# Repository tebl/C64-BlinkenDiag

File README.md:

# C64 BlinkenDiag
I was halfway through sketching out a new PCB based on the details found in an article on [tech.guitarsite.de](http://tech.guitarsite.de/c64_diag_dt_cart.html) before realizing it was already a PCB mentioned at the bottom, more specifically the one by [Diag64cart](https://github.com/svenpetersen1965/Diag64cart) by Sven Petersen (in turn based on [VersaCart64](https://github.com/bwack/Versa64Cart). I did however choose to introduce a few simple features of my own, mainly adding the option of disabling ROM boot - the method used was based on details found on [markus.brenner.de/cartridge](http://markus.brenner.de/cartridge). Secondly, I added a lot of LEDs in the hope that it might in some way be used to detect bus errors.

- [1> Building the unit](#1-building-the-unit)
  - [1.1> Soldering it together](#11-soldering-it-together)
  - [1.2> Assembling the unit](#12-assembling-the-unit)
  - [1.3> Testing it out](#13-testing-it-out)
- [2> Schematic](#2-schematic)
- [3> BOM](#3-bom)

# 1> Building the unit
Building the unit assumes you have at least minor experience soldering things together, recommended is at least a soldering station with adjustable temperature to get started - usually you'll want some 60/40 solder tin (if you can get that where you live). With the equipment sorted, now comes the shopping. So head on over to the [BOM](#3-bom)-section for some information on what you need, with ebay, AliExpress and similar sites you'll need to treat these as a starting search term and get what seems to match the gallery pictures.

## 1.1> Soldering it together
Every part already accounted for? Good, then let's start by not burning the house down (unless it obviously has more than one snake in it). Start by soldering in the resistors, there should only be a few of these on the board - follow it all up by tackling the resistor networks onto the boards, these are all the same type and you should match up the dot on them with the square hole. If you want to install sockets for all of the ICs, then that is good - if not, then please reconsider your life choices about now. Sockets need to match up with the markings on the PCB, indent on the socket should match the half-moon indent on the PCB (use machined sockets if you like that sort of thing).

Add the capacitors that are next to the sockets, these are only for decoupling and are not of the kind that is polarized - personally I tend to solder them in so that, if possible, you can see the printing on the side. The electrolytic capacitor on the bottom left corner, but we need to check that we have a component that will fit first - the faceplate will sit 8mm above the main PCB. If you have one that won't fit, you can lay it on its side instead of waiting for the slow boat from China. Note that this component is polarized, what this means is that you need to match the stripe with the filled in white space on the silkscreen.

Now we need to start the long and arduous task of soldering in all of those LEDs, but before we can do so - you  should probably check that they all work, the easiest way is to just use a CR2032 battery and putting it between the legs of the LED. Testing them will avoid soldering in one that is significantly more dim than the rest, especially if you originally got a whole shopping bag full of them for a single Dollar, Euro, Pound or whatever it is you usually fling at shopping attendants (please don't actually do this). One of the legs is called an anode and the other a cathode, but I can never remember which is which - so I'll just say that the short pin goes into the square hole. Only solder on one of the pins, then flip the board over again and heat up the pin by using your finger to push it flush against the board - this ensures that the faceplate will fit properly and you won't have a board where everything looks crooked.

SW1, 2 and 3 are a common AliExpress variety of DPDT 6-pin switches that needs some further explenation. The ones I've used here have a black base, the ones with a different colour will unfortunately not work as the pinouts have been shuffled around so ensure that you have the correct one ready to go. There is a square hole on the bottom that can be matched to the PCB illustration, just make sure that it goes into place with the hole at the top. There are also some keycaps floating around, but these fit rather loosely and I've taken to adding a drop of glue on the top of the switch to ensure that it doesn't go flying off. The reset switch is a more common momentary switch, the only requirement is that it is long enough to poke through the faceplate (6x6x9mm should fit, get a larger one if you require a bit than just barely).

## 1.2> Assembling the unit
Insert ICs into the sockets as indicated, ensuring that the indent matches the orientation on the board - plugging them in the wrong way ensures that you'll have to order some more. Double-check before even considering plugging it into something, use the picture below as reference. Even more important, study the board under good lighting condition in order to determine whether any stray blobs of solder has ended up in the wrong place - you're supposed to fix your C64, not add to its growing list of problems!

At this point I've not mentioned the EEPROM socket - it is designed for a 28C256, not 27C256 as used in many similar designs (mainly because I hate using UV to erase things and I have enough of them). You'll need an EPROM Programmer to put the machine code onto the chip, the one I use is one of the cheaper options - the MiniPro TL866. Using the *MiniPro Programmer* software (or similar), click the button below *Select IC* and search for 28C256 - find the relevant manufacturer for the chips you have and select the exact chip name. Using *File --> Open...*, browse to a suitable HEX-file such as the one found in the software section of this project (ensure that you download the raw version of this file, not just right click and save as on the github page - as that would save a bunch of html instead of the actual file). Just use the default options for the dialog, then flash the contents into the chip using *Device --> Program*. If this fails, either on write or verification - recheck that you have the correct chip specified, alternatively try another one as ebay chips usually have one or two out of 10 that simply don't work.

The board when plugged into a C64 would more than likely hang out of the connector at an angle, if not 3d-printing a base then I recommend adding some M3 nylon hex standoffs to the bottom of the unit (these should be approximately 16mm in height, alternatively you can combine two 8mm standoffs instead to get the same height) - these can either be F-F or M-F depending on what you have available. The cutouts for LEDs and switches have been designed for a spacing of 8mm between the main module and the faceplate, this should screw onto the 16mm ones you just installed on the bottom. Screw the faceplate onto the main module using standard M3x6mm nylon screws.

The voltmeter module, helpfully only coming with the text *voltage display* printed on them can be installed into the space allotted for it (I picked these up listed as a 0.36" voltage display module in various colours). It has wires sticking out of the bottom, so for the mounting I suggest using some longer M3 nylon screws and adding a nut directly below the module - then installing it on the board, adding two more nuts on the bottom of the main PCB to hold it into place.

## 1.3> Testing it out
With all of the jumpers in their default position, meaning LED outputs are disabled, and the SPDT switches in their upper position - you should get a standard *Diagnostic Cartridge*. Put the **FUNCTION** switch in the lower position and you should get the normal dead test. **ROM_BANK**, when in its lower position will get you a different set of diagnostic tools - depending on the images you flashed your EEPROM with (I specified a 28C256 EEPROM for ease of changing out the contents).

The final switch, labelled **ROM_DIS**, allows you to disable the cartridge detection routines in the C64 - similar to what is done with common cartridge expanders. When pushed the EEPROM is still electrically connected to the C64, but the PLA won't allow the C64 to boot from it - this is here so that you can observe the LED outputs on the machine, while still booting to the standard C64 bootup screen.

# 2> Schematic
The supplied KiCad files should be sufficient as both a schematic and as a  starting point for ordering PCBs (basically you could just zip the contents of the export folder and upload that on a fabrication site), the schematic is also available in [PDF-format](documentation/schematic) and this is what you'll need to print and work your way through this things don't work as expected after assembly.

# 3> BOM
Most parts should be easy to get a hold of from your favourite local electronic component shop, but given that I don't have access to such shops where I live so everything was based on whatever I could get cheapest from eBay/AliExpress (free shipping, but plan on waiting 3-4 weeks for delivery). Values listed in parenthesis are for features that are not required for basic cartridge functionality, but you should read through the section on [building the unit](#1-building-the-unit) to ensure that you're not missing out on anything cool. As always, plan on adding DIP-sockets in addition to the chips listed that have been listed.

| Reference        | Item                                                           | Count | Order  |
| ---------------- | -------------------------------------------------------------- | ----- | ------ |
| PCB              | Fabricate using Gerber files                                   |     1 | [PCBWay](https://www.pcbway.com/project/shareproject/C64_BlinkenDiag.html)
| Faceplate PCB    | Fabricate using Gerber files                                   |    (1)| [PCBWay](https://www.pcbway.com/project/shareproject/C64_BlinkenDiag__faceplate_.html)
| A1               | 0.36" Digital Voltmeter Module                                 |    (1)|
| C1               | 100nF ceramic capacitor (5mm pin spacing)                      |     1 |
| C2-C5            | 100nF ceramic capacitor (5mm pin spacing)                      |    (4)|
| C6               | 10uF 25v electrolytic capacitor (2mm pin spacing)              |    (1)|
| D1-D32           | 5mm LED, preferably non-clear variety                          |   (32)|
| JP1-JP4          | Male breakable pin header (3 pins)                             |    (4)|
| JP1-JP4 Jumpers  | 2.54mm pin header jumper (long type when used with faceplate)  |    (4)|
| R1,R2            | 10k ohm resistor                                               |     2 |
| RN1-RN4          | A331J 8x 330 ohm resistor network (SIP-9)                      |    (4)|
| SW1-SW3          | 6pin 8.5mm x 8.5mm latching switch                             |     3 |
| SW4              | 6x6x8mm momentary switch                                       |    (1)|
| U1               | 28C256 EEPROM (DIP-28)                                         |    (1)|
| U2 *             | 74HCT540 (DIP-20), or 74HCT541 for non-inverting option        |    (1)|
| U3-U5            | 74HCT573 (DIP-20)                                              |    (3)|
| Mounting **      | M3x8mm nylon HEX standoff (F-F)                                |    (4)|
| Mounting **      | M3x16mm nylon HEX standoff (M-F)                               |    (4)|
| Mounting **      | M3x6mm nylon screw                                             |    (4)|
| Mounting **      | M3 nylon nut                                                   |    (4)|
| Mounting ***     | M3 nylon nut                                                   |    (4)|
| Mounting ***     | M3x10mm nylon screw                                            |    (2)|

*) Quite a lot of the CPU signals are active low, the 74HCT540 will invert these signals so that the LED instead lights up when they are active. If you want these to reflect the actual signal, use the non-inverting variant of the chip instead (74HCT541).

**) The standoffs specified are the exact sizes required, but note that you could stack these to obtain the size you need - 8mm + 8mm usually equals 16mm (meaning you only need about 12 of them). Instead of buying the F-F standoffs separately, you could just cut off the screw part on the very bottom.

***) These are used to mount the voltmeter module, an extra nut is used between the module and PCB to avoid destroying the wires underneath the module.

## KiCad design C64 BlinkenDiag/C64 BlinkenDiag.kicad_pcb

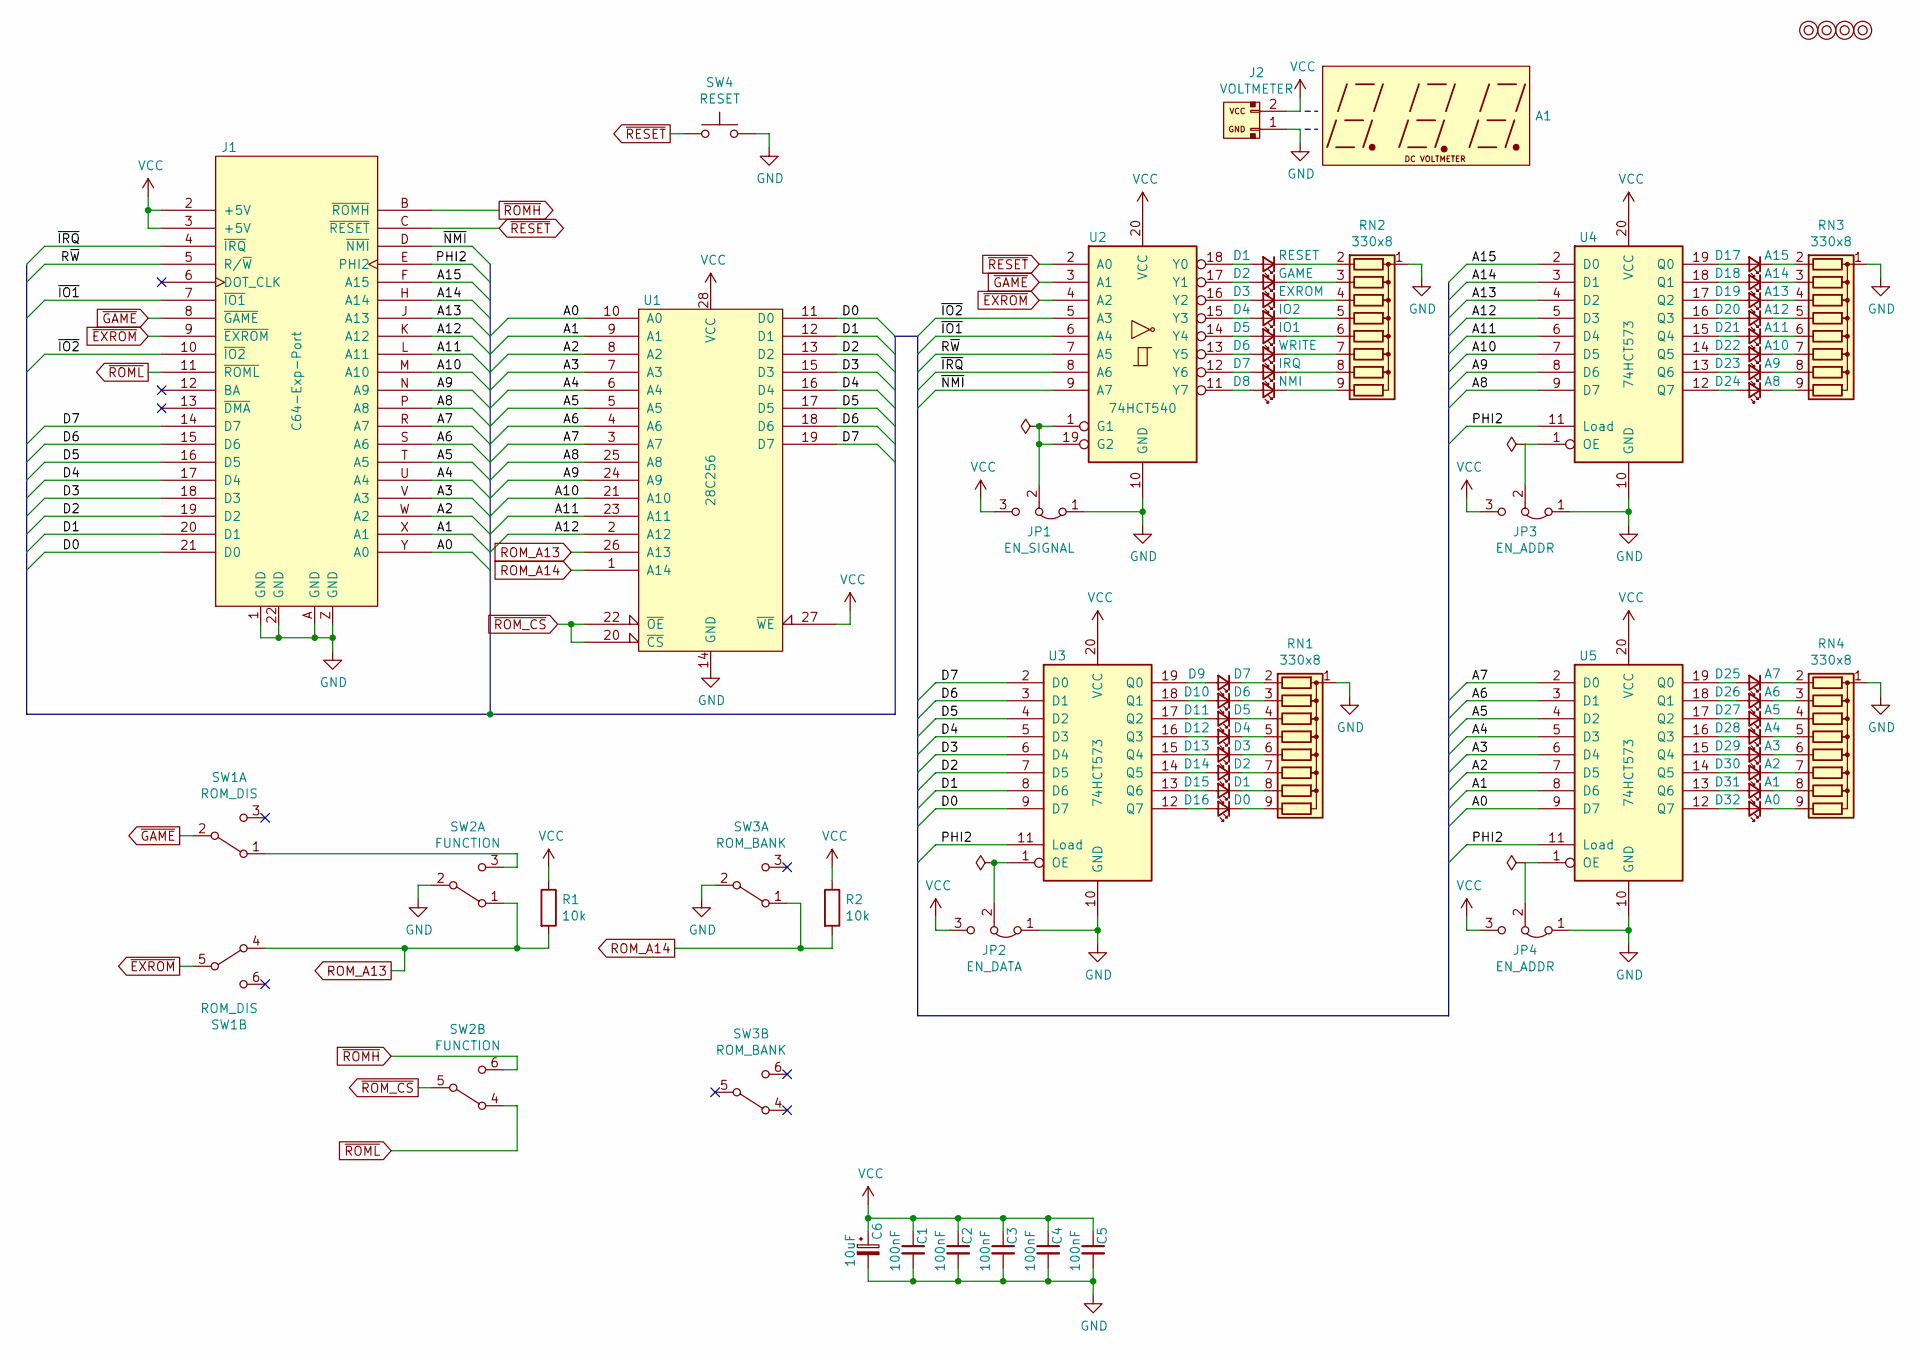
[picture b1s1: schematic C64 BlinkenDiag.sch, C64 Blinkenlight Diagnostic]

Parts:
A1: module; voltage_display_036
C1, C2, C3, C4, C5: 100nF; C_Disc_D4.7mm_W2.5mm_P5.00mm
C6: 10uF; CP_Radial_D4.0mm_P2.00mm
D1: RESET; LED_D5.0mm
D2: GAME; LED_D5.0mm
D3: EXROM; LED_D5.0mm
D4: IO2; LED_D5.0mm
D5: IO1; LED_D5.0mm
D6: WRITE; LED_D5.0mm
D7: IRQ; LED_D5.0mm
D8: NMI; LED_D5.0mm
D9: D7; LED_D5.0mm
D10: D6; LED_D5.0mm
D11: D5; LED_D5.0mm
D12: D4; LED_D5.0mm
D13: D3; LED_D5.0mm
D14: D2; LED_D5.0mm
D15: D1; LED_D5.0mm
D16: D0; LED_D5.0mm
D17: A15; LED_D5.0mm
D18: A14; LED_D5.0mm
D19: A13; LED_D5.0mm
D20: A12; LED_D5.0mm
D21: A11; LED_D5.0mm
D22: A10; LED_D5.0mm
D23: A9; LED_D5.0mm
D24: A8; LED_D5.0mm
D25: A7; LED_D5.0mm
D26: A6; LED_D5.0mm
D27: A5; LED_D5.0mm
D28: A4; LED_D5.0mm
D29: A3; LED_D5.0mm
D30: A2; LED_D5.0mm
D31: A1; LED_D5.0mm
D32: A0; LED_D5.0mm
J1: C64-Exp-Port; C64_Expansion_Port
J2: VOLTMETER; JST_XH_B2B-XH-A_1x02_P2.50mm_Vertical
JP1: EN_SIGNAL; PinHeader_1x03_P2.54mm_Vertical
JP2: EN_DATA; PinHeader_1x03_P2.54mm_Vertical
JP3, JP4: EN_ADDR; PinHeader_1x03_P2.54mm_Vertical
M1, M2, M3, M4: Mounting; M3_pin
R1, R2: 10k; R_Axial_DIN0207_L6.3mm_D2.5mm_P10.16mm_Horizontal
RN1, RN2, RN3, RN4: 330x8; R_Array_SIP9
SW1: ROM_DIS; dpdt_switch_black
SW2: FUNCTION; dpdt_switch_black
SW3: ROM_BANK; dpdt_switch_black
SW4: RESET; SW_PUSH_6mm
U1: 28C256; DIP-28_W15.24mm_Socket_LongPads
U2: 74HCT540; DIP-20_W7.62mm_Socket_LongPads
U3, U4, U5: 74HCT573; DIP-20_W7.62mm_Socket_LongPads

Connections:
/A0: J1.Y (A0), U1.10 (A0), U5.9 (D7)
/A1: J1.X (A1), U1.9 (A1), U5.8 (D6)
/A2: J1.W (A2), U1.8 (A2), U5.7 (D5)
/A3: J1.V (A3), U1.7 (A3), U5.6 (D4)
/A4: J1.U (A4), U1.6 (A4), U5.5 (D3)
/A5: J1.T (A5), U1.5 (A5), U5.4 (D2)
/A6: J1.S (A6), U1.4 (A6), U5.3 (D1)
/A7: J1.R (A7), U1.3 (A7), U5.2 (D0)
/A8: J1.P (A8), U1.25 (A8), U4.9 (D7)
/A9: J1.N (A9), U1.24 (A9), U4.8 (D6)
/A10: J1.M (A10), U1.21 (A10), U4.7 (D5)
/A11: J1.L (A11), U1.23 (A11), U4.6 (D4)
/A12: J1.K (A12), U1.2 (A12), U4.5 (D3)
/A13: J1.J (A13), U4.4 (D2)
/A14: J1.H (A14), U4.3 (D1)
/A15: J1.F (A15), U4.2 (D0)
/D0: J1.21 (D0), U1.11 (D0), U3.9 (D7)
/D1: J1.20 (D1), U1.12 (D1), U3.8 (D6)
/D2: J1.19 (D2), U1.13 (D2), U3.7 (D5)
/D3: J1.18 (D3), U1.15 (D3), U3.6 (D4)
/D4: J1.17 (D4), U1.16 (D4), U3.5 (D3)
/D5: J1.16 (D5), U1.17 (D5), U3.4 (D2)
/D6: J1.15 (D6), U1.18 (D6), U3.3 (D1)
/D7: J1.14 (D7), U1.19 (D7), U3.2 (D0)
/PHI2: J1.E (PHI2), U3.11 (Load), U4.11 (Load), U5.11 (Load)
/R~W: J1.5 (R/~W), U2.7 (A5)
/~IO1: J1.7 (~IO1), U2.6 (A4)
/~IO2: J1.10 (~IO2), U2.5 (A3)
/~IRQ: J1.4 (~IRQ), U2.8 (A6)
/~NMI: J1.D (~NMI), U2.9 (A7)
GND: C1.2, C2.2, C3.2, C4.2, C5.2, C6.2, J1.1 (GND), J1.22 (GND), J1.A (GND), J1.Z (GND), J2.1, JP1.1 (A), JP2.1 (A), JP3.1 (A), JP4.1 (A), RN1.1 (common), RN2.1 (common), RN3.1 (common), RN4.1 (common), SW2.2 (B), SW3.2 (B), SW4.2, U1.14 (GND), U2.10 (GND), U3.10 (GND), U4.10 (GND), U5.10 (GND)
unnamed: D1.1 (K), RN2.2 (R1)
unnamed: D1.2 (A), U2.18 (Y0)
unnamed: D2.1 (K), RN2.3 (R2)
unnamed: D2.2 (A), U2.17 (Y1)
unnamed: D3.1 (K), RN2.4 (R3)
unnamed: D3.2 (A), U2.16 (Y2)
unnamed: D4.1 (K), RN2.5 (R4)
unnamed: D4.2 (A), U2.15 (Y3)
unnamed: D5.1 (K), RN2.6 (R5)
unnamed: D5.2 (A), U2.14 (Y4)
unnamed: D6.1 (K), RN2.7 (R6)
unnamed: D6.2 (A), U2.13 (Y5)
unnamed: D7.1 (K), RN2.8 (R7)
unnamed: D7.2 (A), U2.12 (Y6)
unnamed: D8.1 (K), RN2.9 (R8)
unnamed: D8.2 (A), U2.11 (Y7)
unnamed: D9.1 (K), RN1.2 (R1)
unnamed: D9.2 (A), U3.19 (Q0)
unnamed: D10.1 (K), RN1.3 (R2)
unnamed: D10.2 (A), U3.18 (Q1)
unnamed: D11.1 (K), RN1.4 (R3)
unnamed: D11.2 (A), U3.17 (Q2)
unnamed: D12.1 (K), RN1.5 (R4)
unnamed: D12.2 (A), U3.16 (Q3)
unnamed: D13.1 (K), RN1.6 (R5)
unnamed: D13.2 (A), U3.15 (Q4)
unnamed: D14.1 (K), RN1.7 (R6)
unnamed: D14.2 (A), U3.14 (Q5)
unnamed: D15.1 (K), RN1.8 (R7)
unnamed: D15.2 (A), U3.13 (Q6)
unnamed: D16.1 (K), RN1.9 (R8)
unnamed: D16.2 (A), U3.12 (Q7)
unnamed: D17.1 (K), RN3.2 (R1)
unnamed: D17.2 (A), U4.19 (Q0)
unnamed: D18.1 (K), RN3.3 (R2)
unnamed: D18.2 (A), U4.18 (Q1)
unnamed: D19.1 (K), RN3.4 (R3)
unnamed: D19.2 (A), U4.17 (Q2)
unnamed: D20.1 (K), RN3.5 (R4)
unnamed: D20.2 (A), U4.16 (Q3)
unnamed: D21.1 (K), RN3.6 (R5)
unnamed: D21.2 (A), U4.15 (Q4)
unnamed: D22.1 (K), RN3.7 (R6)
unnamed: D22.2 (A), U4.14 (Q5)
unnamed: D23.1 (K), RN3.8 (R7)
unnamed: D23.2 (A), U4.13 (Q6)
unnamed: D24.1 (K), RN3.9 (R8)
unnamed: D24.2 (A), U4.12 (Q7)
unnamed: D25.1 (K), RN4.2 (R1)
unnamed: D25.2 (A), U5.19 (Q0)
unnamed: D26.1 (K), RN4.3 (R2)
unnamed: D26.2 (A), U5.18 (Q1)
unnamed: D27.1 (K), RN4.4 (R3)
unnamed: D27.2 (A), U5.17 (Q2)
unnamed: D28.1 (K), RN4.5 (R4)
unnamed: D28.2 (A), U5.16 (Q3)
unnamed: D29.1 (K), RN4.6 (R5)
unnamed: D29.2 (A), U5.15 (Q4)
unnamed: D30.1 (K), RN4.7 (R6)
unnamed: D30.2 (A), U5.14 (Q5)
unnamed: D31.1 (K), RN4.8 (R7)
unnamed: D31.2 (A), U5.13 (Q6)
unnamed: D32.1 (K), RN4.9 (R8)
unnamed: D32.2 (A), U5.12 (Q7)
unnamed: JP1.2 (C), U2.1 (G1), U2.19 (G2)
unnamed: JP2.2 (C), U3.1 (OE)
unnamed: JP3.2 (C), U4.1 (OE)
unnamed: JP4.2 (C), U5.1 (OE)
unnamed: SW1.1 (A), SW2.3 (C)
ROM_A13: R1.2, SW1.4 (A), SW2.1 (A), U1.26 (A13)
ROM_A14: R2.2, SW3.1 (A), U1.1 (A14)
VCC: C1.1, C2.1, C3.1, C4.1, C5.1, C6.1, J1.2 (+5V), J1.3 (+5V), J2.2, JP1.3 (B), JP2.3 (B), JP3.3 (B), JP4.3 (B), R1.1, R2.1, U1.27 (~WE), U1.28 (VCC), U2.20 (VCC), U3.20 (VCC), U4.20 (VCC), U5.20 (VCC)
~EXROM: J1.9 (~EXROM), SW1.5 (B), U2.4 (A2)
~GAME: J1.8 (~GAME), SW1.2 (B), U2.3 (A1)
~RESET: J1.C (~RESET), SW4.1, U2.2 (A0)
~ROMH: J1.B (~ROMH), SW2.6 (C)
~ROML: J1.11 (~ROML), SW2.4 (A)
~ROM_CS: SW2.5 (B), U1.20 (~CS), U1.22 (~OE)

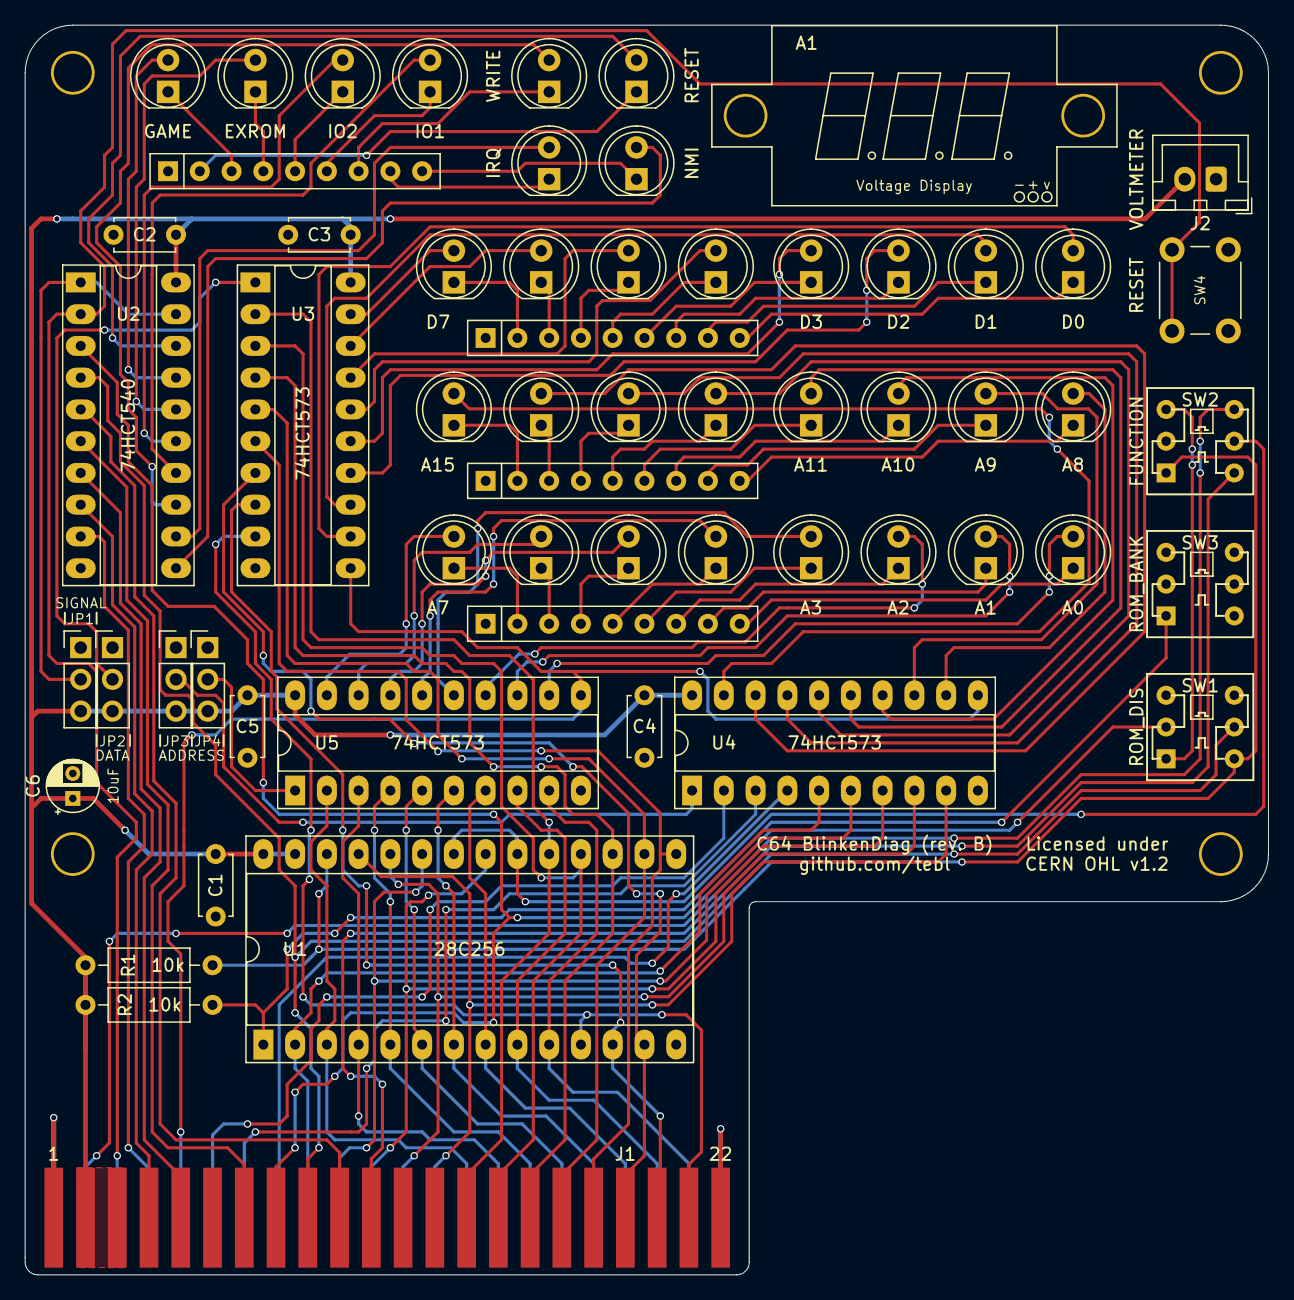
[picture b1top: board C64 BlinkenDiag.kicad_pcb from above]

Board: 2 copper layers, 99.4 x 99.9 mm, 64 parts (0 on the bottom side), 109 nets.

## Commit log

2021-02-17 Added cartridge schematic
2021-02-17 Added switch to disable ROM
2021-02-17 Added voltmeter module and mounting library
2021-02-17 Assign footprints
2021-02-17 Edges and mounting added
2021-02-19 Did a layout
2021-02-19 Tweaked silkscreen and gerber export
2021-02-19 README updated
2021-02-22 Add PCB preview
2021-03-15 Added faceplate and changed ROM_EN to ROM_DIS
2021-03-15 Added images
2021-03-16 Added BOM
2021-03-16 Added orientation for the black switches
2021-03-16 Added some images
2021-03-16 Added image
2021-03-16 Added keycaps
2021-03-17 Updated gerber files
2021-03-17 Added PCBway links
2021-04-09 Improved switch description slightly

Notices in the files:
C64 BlinkenDiag/C64 BlinkenDiag.kicad_pcb:
Licensed under
CERN OHL v1.2
